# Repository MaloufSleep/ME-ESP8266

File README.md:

# ME-ESP8266
Malouf Electronics - ESP8266 Dev Board

The ultimate ESP8266 development board built by makers for makers.

[Malouf Electronics website](https://www.maloufelectronics.com)

## SPECIFICATIONS / FEATURES

* 16 MB Flash
* 5V Relay
* RS232 interface
* IR Receiver
* IR LED
* Terminal Block for Power & RS232
* Terminal Block for Relay
* Easily accessible GPIO
* Micro USB (power & programming)

## GETTING STARTED
1. Download Arduino IDE (https://www.arduino.cc/en/Main/Software)
2. Setup ESP8266 support for Arduino IDE:
* Start Arduino and open Preferences window.
* Enter https://arduino.esp8266.com/stable/package_esp8266com_index.json into the Additional Board Manager URLs field.
* Open Boards Manager from the Tools > Board menu and find esp8266 platform.
* Select the version you need from the drop-down box.
* Click the Install button.
* Don't forget to select your ESP8266 board from the Tools > Board menu after installation.
3. Select "Generic ESP8266 Module"
4. Pick the following from the Tools menu:
* Upload Speed: 115200
* CPU Frequency: 80MHz
* Crystal Frequency: 26MHz
* Flash Size: 16MB
* Flash Mode: DOUT
* Flash Frequency: 40MHz
* Port: (the serial port of your USB cable)
5. Paste the code below into a new sketch and upload to the board (In order to upload you may have to hold the boot button until esptool connects):

```
const int LED_RED = 5;

void setup() {
    pinMode(LED_RED, OUTPUT);     // setup red LED as output
}

void loop() {

    digitalWrite(LED_RED, LOW);   // turn the LED on
    delay(1000);                  // wait for a second

    digitalWrite(LED_RED, HIGH);  // turn the LED off
    delay(1000);                  // wait for a second

}
```

If all goes well the board will program and the red LED will start blinking.

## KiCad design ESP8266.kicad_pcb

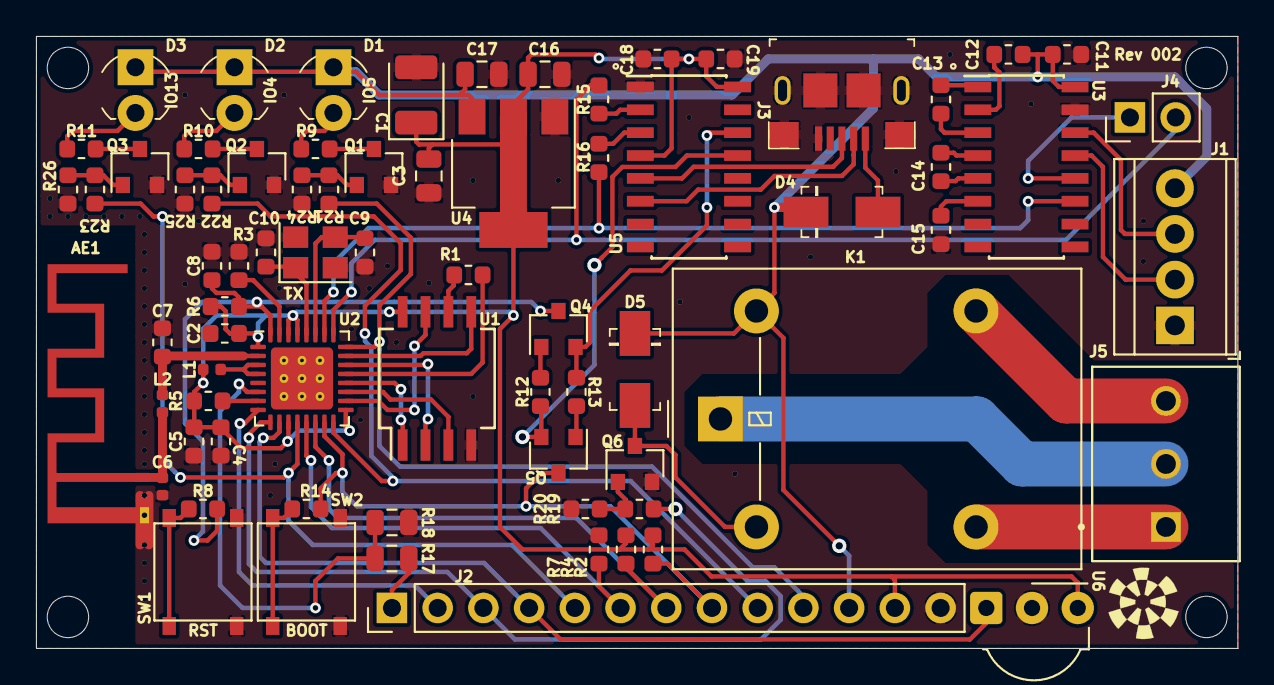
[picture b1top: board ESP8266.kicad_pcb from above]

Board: 2 copper layers, 66.8 x 34.0 mm, 74 parts (0 on the bottom side), 65 nets.

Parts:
AE1: Antenna_Shield; Texas_SWRA117D_2.4GHz_Right
C1: TAJB107K006RNJ; CP_EIA-3528-15_AVX-H
C2, C8, C11, C18, C19: CC0603KRX7R9BB104; C_0603_1608Metric
C3, C16, C17: CL21A106KAYNNNE; C_0805_2012Metric
C4, C5, C12, C13, C14, C15: CL10A105KB8NNNC; C_0603_1608Metric
C6: 0402CG2R7C500NT; C_0402_1005Metric
C7: 0603CG3R0C500NT; C_0603_1608Metric
C9, C10: 0603CG6R8C500NT; C_0603_1608Metric
D1: QBL7SA60D; LED_3mm_Radial
D2: QBL7IG60D; LED_3mm_Radial
D3: TSHA440; LED_3mm_Radial
D4: SS14; DO-214AC
D5: GF1A; DO-214AC
J1: 282834-4; TerminalBlock_TE_282834-4_1x04_P2.54mm_Horizontal
J2: 68000-113HLF; PinHeader_1x13_P2.54mm_Vertical
J3: 10118193-0001LF; USB_Micro_B_Female_10118193-0001LF
J4: 68000-102HLF; PinHeader_1x02_P2.54mm_Vertical
J5: 284391-3; TE_284391-3
K1: G5LE-1; Relay_SPDT_Omron-G5LE-1
L1: SDCL1005C4N3STDF; L_0402_1005Metric
L2: LQG15HS2N2S02D; L_0402_1005Metric
Q1, Q2, Q3, Q6: AO3400A; SOT-23
Q4, Q5: S8050_SMD; SOT-23
R1: 0603WAF2000T5E; R_0603_1608Metric
R2, R4, R5, R6, R7, R12, R13, R20, R24, R25, R26: 0603WAF1002T5E; R_0603_1608Metric
R3: 0603WAF1202T5E; R_0603_1608Metric
R8, R14, R15, R16, R19, R21, R22, R23: 0603WAF4700T5E; R_0603_1608Metric
R9, R10, R11: 0603WAF620JT5E; R_0603_1608Metric
R17: 0805W8F2203T5E; R_0805_2012Metric
R18: 0805W8F8202T5E; R_0805_2012Metric
SW1, SW2: TS-1187A-B-A-B
U1: W25Q128JVSIQ; SO-8_5.3x6.2mm_P1.27mm
U2: ESP8266EX; QFN-32-1EP_5x5mm_P0.5mm_EP3.45x3.45mm_ThermalVias
U3: MAX232ESE+T; SOIC-16_3.9x9.9mm_P1.27mm
U4: NCP1117-3.3_SOT223; SOT-223-3_TabPin2
U5: CH340C; SOIC-16_3.9x9.9mm_P1.27mm
U6: VS1838B; Vishay_MOLD-3Pin
X1: X1E000021081900; Crystal_SMD_3225-4Pin_3.2x2.5mm

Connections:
+3V3: C1.1, C2.1, C3.2, C4.1, C5.2, C16.1, C18.1, C19.2, J2.12, L1.1, R2.2, R4.2, R5.2, R6.2, U1.8, U2.1, U2.11, U2.17, U2.29, U2.30, U4.2, U5.4, U5.16, U6.3
+5V: C11.1, C12.2, C17.1, D1.1, D2.1, D3.1, D4.K, D5.K, J1.4, J2.11, K1.5, U3.16, U4.3
/ANT: AE1.1, C6.2, L2.2
/EN: R5.1, U2.7
/GPIO0: J2.8, Q5.3, R2.1, R14.1, U2.15
/GPIO2: J2.7, R4.1, U2.14
/GPIO4: J2.9, R22.2, U2.16
/GPIO5: J2.10, R21.2, U2.24
/GPIO12: J2.4, U2.10, U6.1
/GPIO13: J2.5, R23.2, U2.12
/GPIO14: J2.3, R19.1, U2.9
/GPIO15: J2.6, R7.1, U2.13
/GPIO16: J2.2, U2.8
/LNA: C7.2, L2.1, U2.2
/RS232/RX_RS232: J1.2, U3.13
/RS232/TX_RS232: J1.3, U3.14
/RX: J4.2, R15.1, U2.25
/Relay/COM: J5.2, K1.1
/Relay/NC: J5.3, K1.4
/Relay/NO: J5.1, K1.3
/SD_CLK: R1.1, U1.6
/SD_CMD: U1.1, U2.20
/SD_D0: U1.2, U2.22
/SD_D1: U1.5, U2.23
/SD_D2: U1.7, U2.18
/SD_D3: U1.3, U2.19
/TOUT: R17.1, R18.2, U2.6
/TOUT_EX: J2.1, R17.2
/TX: R16.1, U2.26, U3.11
/USBtoSerial/D_N: J3.2, U5.6
/USBtoSerial/D_P: J3.3, U5.5
/~DTR: Q5.2, R12.1, U5.13
/~RST: C8.1, Q4.3, R6.1, R8.1, U2.32
/~RTS: Q4.2, R13.1, U5.14
GND: AE1.2, C1.2, C2.2, C3.1, C4.2, C5.1, C6.1, C7.1, C8.2, C9.1, C10.2, C11.2, C15.1, C16.2, C17.2, C18.2, C19.1, J1.1, J2.13, J3.5, J3.SH, Q1.2, Q2.2, Q3.2, Q6.2, R3.2, R7.2, R18.1, R20.1, R24.1, R25.1, R26.1, SW1.3, SW1.4, SW2.3, SW2.4, U1.4, U2.33, U3.15, U4.1, U5.1, U6.2, X1.2, X1.4
unnamed: C9.2, U2.27, X1.3
unnamed: C10.1, U2.28, X1.1
unnamed: C12.1, U3.2
unnamed: C13.1, U3.1
unnamed: C13.2, U3.3
unnamed: C14.1, U3.4
unnamed: C14.2, U3.5
unnamed: C15.2, U3.6
unnamed: D1.2, R9.1
unnamed: D2.2, R10.1
unnamed: D3.2, R11.1
unnamed: D4.A, J3.1
unnamed: D5.A, K1.2, Q6.3
unnamed: J4.1, U3.12
unnamed: L1.2, U2.3, U2.4
unnamed: Q1.1, R21.1, R24.2
unnamed: Q1.3, R9.2
unnamed: Q2.1, R22.1, R25.2
unnamed: Q2.3, R10.2
unnamed: Q3.1, R23.1, R26.2
unnamed: Q3.3, R11.2
unnamed: Q4.1, R12.2
unnamed: Q5.1, R13.2
unnamed: Q6.1, R19.2, R20.2
unnamed: R1.2, U2.21
unnamed: R3.1, U2.31
unnamed: R8.2, SW1.1, SW1.2
unnamed: R14.2, SW2.1, SW2.2
unnamed: R15.2, U5.2
unnamed: R16.2, U5.3

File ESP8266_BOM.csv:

Designator,Quantity,Value,LCSC Part #,Footprint,Notes
"C1, ",1,TAJB107K006RNJ,C16133,Capacitor_Tantalum_SMD:CP_EIA-3528-15_AVX-H,
"C3, C16, C17, ",3,CL21A106KAYNNNE,C15850,Capacitor_SMD:C_0805_2012Metric,
"C4, C5, C13, C14, C15, C12, ",6,CL10A105KB8NNNC,C15849,Capacitor_SMD:C_0603_1608Metric,
"C6, ",1,0402CG2R7C500NT,C1561,Capacitor_SMD:C_0402_1005Metric,
"C7, ",1,0603CG3R0C500NT,C46219,Capacitor_SMD:C_0603_1608Metric,
"C8, C2, C11, C18, C19, ",5,CC0603KRX7R9BB104,C14663,Capacitor_SMD:C_0603_1608Metric,
"C9, C10, ",2,0603CG6R8C500NT,C1679,Capacitor_SMD:C_0603_1608Metric,
"D4, ",1,SS14,C2480,Diode_SMD:DO-214AC,
"D5, ",1,M7,C95872,Diode_SMD:DO-214AC,
"L1, ",1,SDCL1005C4N3STDF,C52051,Inductor_SMD:L_0402_1005Metric,
"L2, ",1,LQG15HS2N2S02D,C86061,Inductor_SMD:L_0402_1005Metric,
"Q2, Q3, Q6, Q1, ",4,AO3400A,C20917,Package_TO_SOT_SMD:SOT-23,
"Q4, Q5, ",2,S8050_SMD,C2146,Package_TO_SOT_SMD:SOT-23,
"R1, ",1,0603WAF2000T5E,C8218,Resistor_SMD:R_0603_1608Metric,
"R2, R4, R5, R6, R7, R12, R13, R24, R25, R26, R20, ",11,0603WAF1002T5E,C25804,Resistor_SMD:R_0603_1608Metric,
"R3, ",1,0603WAF1202T5E,C22790,Resistor_SMD:R_0603_1608Metric,
"R8, R14, R23, R22, R21, R19, R15, R16, ",8,0603WAF4700T5E,C23179,Resistor_SMD:R_0603_1608Metric,
"R9, R11, R10, ",3,0603WAF620JT5E,C23222,Resistor_SMD:R_0603_1608Metric,
"R17, ",1,0805W8F2203T5E,C17556,Resistor_SMD:R_0805_2012Metric,
"R18, ",1,0805W8F8202T5E,C17840,Resistor_SMD:R_0805_2012Metric,
"SW1, SW2, ",2,TS-1187A-B-A-B,C318884,Button_Switch_SMD:TS-1187A-B-A-B,
"U1, ",1,W25Q128JVSIQ,C97521,Package_SO:SO-8_5.3x6.2mm_P1.27mm,
"U2, ",1,ESP8266EX,C77967,Package_DFN_QFN:QFN-32-1EP_5x5mm_P0.5mm_EP3.45x3.45mm_ThermalVias,
"U3, ",1,MAX232ESE+T,C26860,Package_SO:SOIC-16_3.9x9.9mm_P1.27mm,
"U4, ",1,NCP1117-3.3_SOT223,C26537,Package_TO_SOT_SMD:SOT-223-3_TabPin2,
"U5, ",1,CH340C,C84681,Package_SO:SOIC-16_3.9x9.9mm_P1.27mm,
"X1, ",1,X1E000021081900,C91747,Crystal:Crystal_SMD_3225-4Pin_3.2x2.5mm,
D1,1,QBL7SA60D,,LED_3mm_Radial,substitution okay
D2,1,QBL7IG60D,,LED_3mm_Radial,substitution okay
D3,1,TSHA4400,,LED_3mm_Radial,substitution okay
"J1, ",1,282834-4,,TerminalBlock_TE-Connectivity:TerminalBlock_TE_282834-4_1x04_P2.54mm_Horizontal,substitution okay
"J2, ",1,68000-113HLF,,Connector_PinHeader_2.54mm:PinHeader_1x13_P2.54mm_Vertical,substitution okay
"J3, ",1,10118193-0001LF,,digikey-footprints:USB_Micro_B_Female_10118193-0001LF,substitution okay
"J4, ",1,68000-102HLF,,Connector_PinHeader_2.54mm:PinHeader_1x02_P2.54mm_Vertical,substitution okay
"J5, ",1,284391-3,,TerminalBlock_TE-Connectivity:TE_284391-3,substitution okay
"K1, ",1,G5LE-14 DC5,,Relay_THT:Relay_SPDT_Omron-G5LE-1,substitution okay
"U6, ",1,VS1838B,,OptoDevice:Vishay_MOLD-3Pin,substitution okay

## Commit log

2020-10-13 Update README.md
    Add note about what I had to do to make my MaloufSleep esp8266 work.
